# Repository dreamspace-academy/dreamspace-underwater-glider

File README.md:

# Underwater Glider

## **Motivation**

### Blue Econemy
Sri Lanka is an island country, located in the Indian Ocean, with a coastline of 1,585 km long, and the country claims an Exclusive Economic Zone (EEZ) extending 200 nautical miles, which is approximately 6.7 times Sri Lanka's land area. [1]

### Life Below Water
The world’s waters – their temperature, chemistry, currents and life – drive global systems that make the Earth habitable. How we manage this vital resource is essential for life on earth, and to counterbalance the effects of climate change. [2]

## **Problem**

### Real-time Monitoring
To keep our water ecosystem safe, secure, clean and sustainable, we need to measure various parameters in real-time. Sri Lanka, being a country that was devastated by 30 years of war, doesn’t even have the basic infrastructure, such as roads, in many parts of the country.

Therefore it is understandable that there is no modern infrastructure in Sri Lanka to measure and monitor the water ecosystems. Such equipment is very crucial for scientific research and assessment on an ecosystem, which is swiftly changing due to various weather conditions. [3]

### Affordability
The coastline and adjacent waters support highly productive marine ecosystems, and provide a massive economic value to this small nation, while this unique geographical position is highly contested by global powers.

## **Solution**

### Open-source Underwater Glider (OSUG)
There has been a breakthrough with low cost autonomous underwater vehicles, and as this capability has matured a wide range of hobby and commercial applications have been developed. However, there are no affordable extended duration underwater exploration platforms and this project aims to address this need.

Alex Williams, a young innovator from the USA, has developed a low cost and versatile underwater glider capable of extended missions of up to weeks at a time; using commodity hardware, 3D printed parts and an open-source autopilot. Furthermore, he won the Grand Prize in the Hackaday Prize Challenge 2017. [4]

### Underwater Gliding
Underwater gliders use a buoyancy engine to change the mass of the glider, allowing them to ascend and descend through the water. With power only being used to power the engine intermittently, gliders can typically run for weeks or months without recharge, making them ideal for environmental monitoring. As underwater gliders travel slowly through the water, they disturb the surrounding water very little, allowing for accurate and reliable data recording. [5]

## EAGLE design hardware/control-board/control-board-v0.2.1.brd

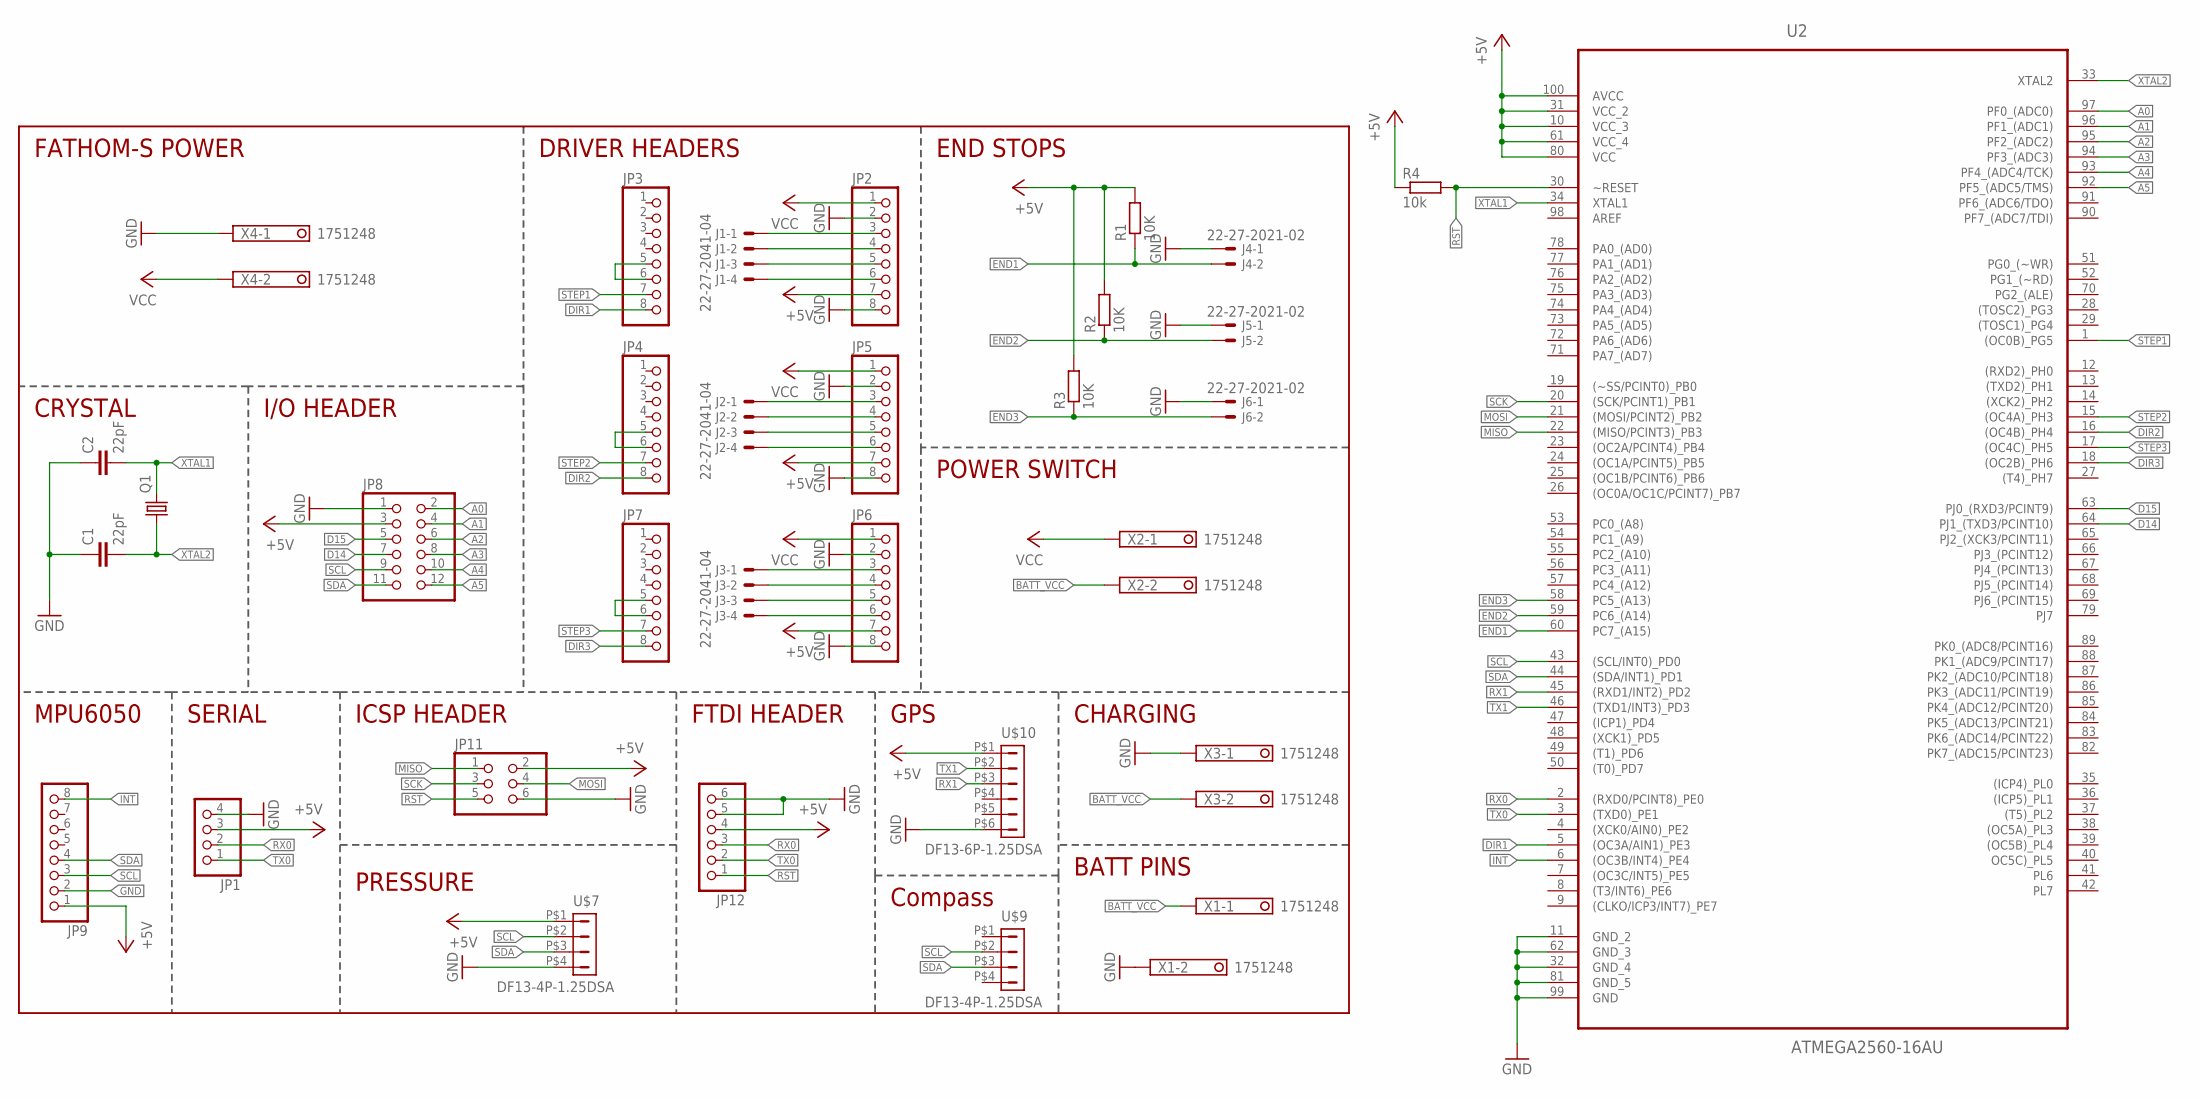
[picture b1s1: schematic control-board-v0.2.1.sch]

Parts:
C1, C2: 22pF; C0603
J1, J2, J3: 22-27-2041-04; 6410-04
J4, J5, J6: 22-27-2021-02; 6410-02
JP1: PINHD-1X4; 1X04
JP2, JP3, JP4, JP5, JP6, JP7, JP9: PINHD-1X8; 1X08
JP8: PINHD-2X6; 2X06
JP11: PINHD-2X3; 2X03
JP12: PINHD-1X6; 1X06
Q1: CRYSTALHC49U70; HC49U70
R1, R2, R3: 10K; R0603
R4: 10k; R0603
U2: ATMEGA2560-16AU; QFP50P1600X1600X120-100N
U$7, U$9: DF13-4P-1.25DSA
U$10: DF13-6P-1.25DSA
X1, X2, X3, X4: 1751248

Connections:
+5V: JP1.3, JP2.7, JP5.7, JP6.7, JP8.3, JP9.1, JP11.2, JP12.4, R1.2, R2.2, R3.2, R4.1, U2.10 (VCC_3), U2.31 (VCC_2), U2.61 (VCC_4), U2.80 (VCC), U2.100 (AVCC), U$7.P$1 (1), U$10.P$1 (1)
A0: JP8.2, U2.97 (PF0_(ADC0))
A1: JP8.4, U2.96 (PF1_(ADC1))
A2: JP8.6, U2.95 (PF2_(ADC2))
A3: JP8.8, U2.94 (PF3_(ADC3))
A4: JP8.10, U2.93 (PF4_(ADC4/TCK))
A5: JP8.12, U2.92 (PF5_(ADC5/TMS))
BATT_VCC: X1.1, X2.2, X3.2
D14: JP8.7, U2.64 (PJ1_(TXD3/PCINT10))
D15: JP8.5, U2.63 (PJ0_(RXD3/PCINT9))
DIR1: JP3.8, U2.5 ((OC3A/AIN1)_PE3)
DIR2: JP4.8, U2.16 ((OC4B)_PH4)
DIR3: JP7.8, U2.18 ((OC2B)_PH6)
END1: J4.2, R1.1, U2.60 (PC7_(A15))
END2: J5.2, R2.1, U2.59 (PC6_(A14))
END3: J6.2, R3.1, U2.58 (PC5_(A13))
GND: C1.1, C2.1, J4.1, J5.1, J6.1, JP1.4, JP2.2, JP2.8, JP5.2, JP5.8, JP6.2, JP6.8, JP8.1, JP9.2, JP11.6, JP12.5, JP12.6, U2.11 (GND_2), U2.32 (GND_4), U2.62 (GND_3), U2.81 (GND_5), U2.99 (GND), U$7.P$4 (4), U$10.P$6 (6), X1.2, X3.1, X4.1
INT: JP9.8, U2.6 ((OC3B/INT4)_PE4)
MISO: JP11.1, U2.22 ((MISO/PCINT3)_PB3)
MOSI: JP11.4, U2.21 ((MOSI/PCINT2)_PB2)
unnamed: JP3.5, JP3.6
unnamed: JP4.5, JP4.6
unnamed: J1.4, JP2.6
unnamed: JP7.5, JP7.6
unnamed: J1.3, JP2.5
unnamed: J1.2, JP2.4
unnamed: J1.1, JP2.3
unnamed: J2.4, JP5.6
unnamed: J2.3, JP5.5
unnamed: J2.2, JP5.4
unnamed: J2.1, JP5.3
unnamed: J3.4, JP6.6
unnamed: J3.3, JP6.5
unnamed: J3.2, JP6.4
unnamed: J3.1, JP6.3
RST: JP11.5, JP12.1, R4.2, U2.30 (~RESET)
RX0: JP1.2, JP12.3, U2.2 ((RXD0/PCINT8)_PE0)
RX1: U2.45 ((RXD1/INT2)_PD2), U$10.P$3 (3)
SCK: JP11.3, U2.20 ((SCK/PCINT1)_PB1)
SCL: JP8.9, JP9.3, U2.43 ((SCL/INT0)_PD0), U$7.P$2 (2), U$9.P$2 (2)
SDA: JP8.11, JP9.4, U2.44 ((SDA/INT1)_PD1), U$7.P$3 (3), U$9.P$3 (3)
STEP1: JP3.7, U2.1 ((OC0B)_PG5)
STEP2: JP4.7, U2.15 ((OC4A)_PH3)
STEP3: JP7.7, U2.17 ((OC4C)_PH5)
TX0: JP1.1, JP12.2, U2.3 ((TXD0)_PE1)
TX1: U2.46 ((TXD1/INT3)_PD3), U$10.P$2 (2)
VCC: JP2.1, JP5.1, JP6.1, X2.1, X4.2
XTAL1: C2.2, Q1.2, U2.34 (XTAL1)
XTAL2: C1.2, Q1.1, U2.33 (XTAL2)

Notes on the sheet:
MPU6050
DRIVER HEADERS
BATT PINS
END STOPS
SERIAL
ICSP HEADER
FTDI HEADER
GPS
Compass
CHARGING
PRESSURE
POWER SWITCH
FATHOM-S POWER
CRYSTAL
I/O HEADER

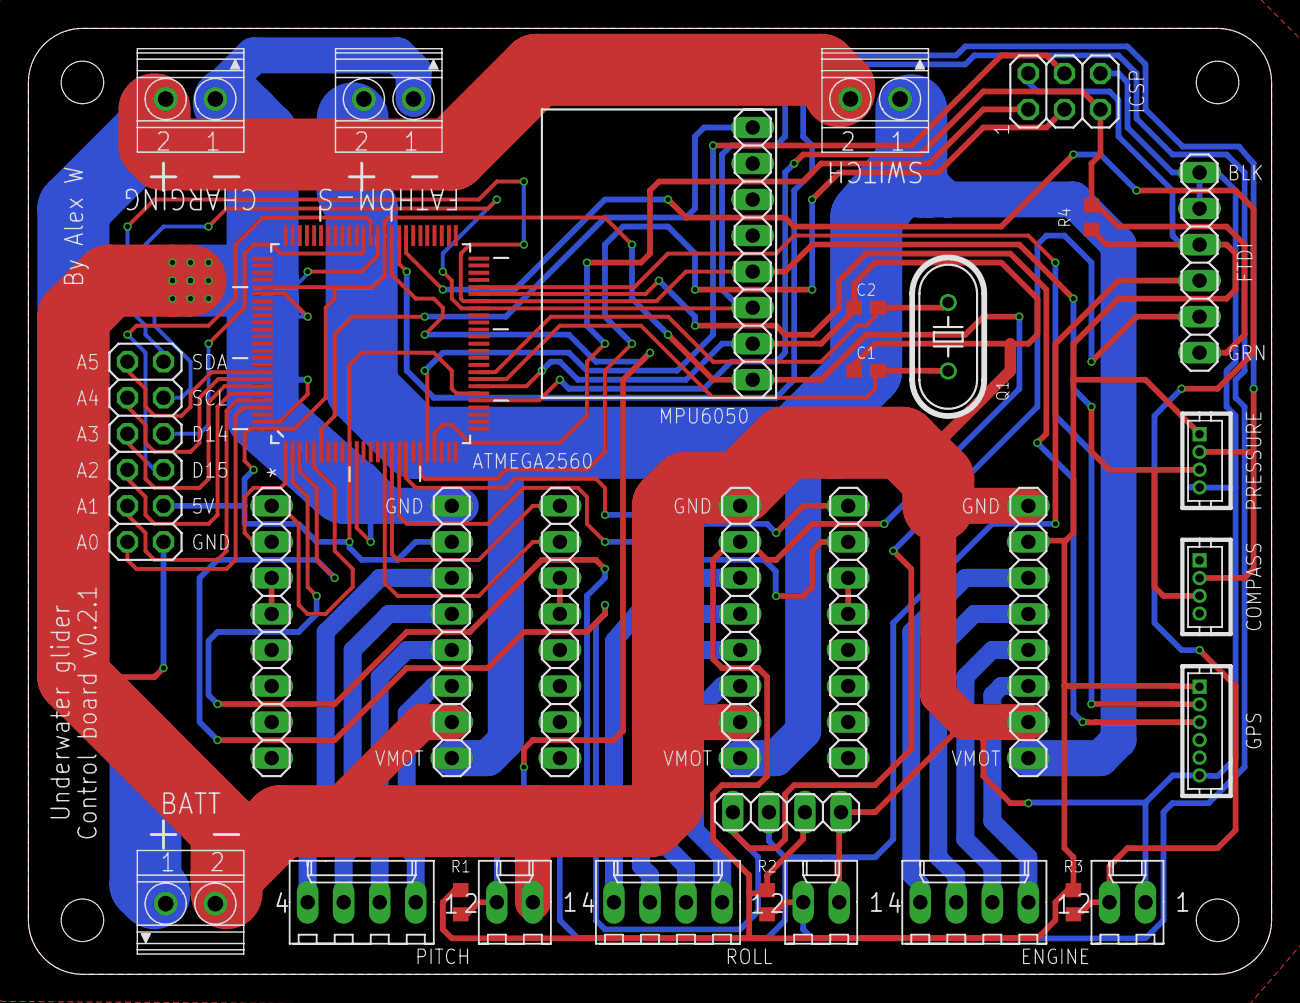
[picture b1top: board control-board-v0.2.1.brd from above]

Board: 2 copper layers, 87.6 x 66.7 mm, 32 parts (0 on the bottom side), 49 nets.

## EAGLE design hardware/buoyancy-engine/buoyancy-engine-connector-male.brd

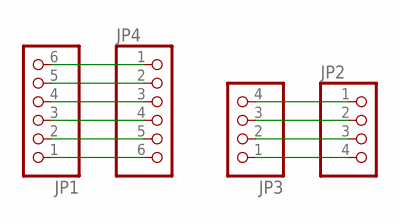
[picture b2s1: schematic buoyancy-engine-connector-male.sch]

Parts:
JP1, JP4: PINHD-1X6; 1X06
JP2, JP3: PINHD-1X4; 1X04

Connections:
unnamed: JP2.1, JP3.4
unnamed: JP2.2, JP3.3
unnamed: JP2.3, JP3.2
unnamed: JP2.4, JP3.1
unnamed: JP1.6, JP4.1
unnamed: JP1.5, JP4.2
unnamed: JP1.4, JP4.3
unnamed: JP1.3, JP4.4
unnamed: JP1.2, JP4.5
unnamed: JP1.1, JP4.6

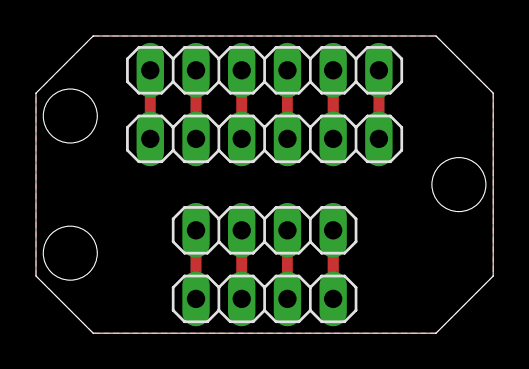
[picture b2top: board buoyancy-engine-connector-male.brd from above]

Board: 2 copper layers, 25.4 x 16.5 mm, 4 parts (0 on the bottom side), 10 nets.

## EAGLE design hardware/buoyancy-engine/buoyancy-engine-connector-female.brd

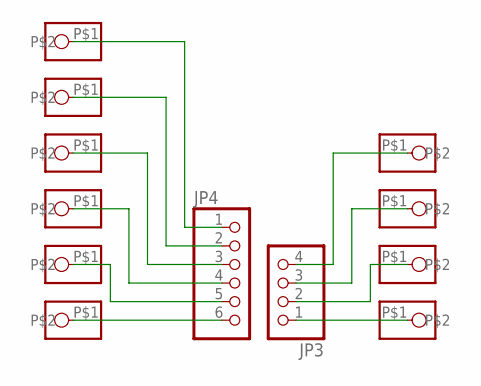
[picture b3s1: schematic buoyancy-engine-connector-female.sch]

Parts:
JP3: PINHD-1X4; 1X04
JP4: PINHD-1X6; 1X06
U$1, U$2, U$3, U$4, U$5, U$6, U$7, U$8, U$9, U$10: POGO-PIN-PAD

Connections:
unnamed: JP3.4, U$10.P$1
unnamed: JP3.3, U$7.P$1
unnamed: JP3.2, U$8.P$1
unnamed: JP3.1, U$9.P$1
unnamed: JP4.1, U$6.P$1
unnamed: JP4.2, U$5.P$1
unnamed: JP4.3, U$4.P$1
unnamed: JP4.4, U$3.P$1
unnamed: JP4.5, U$2.P$1
unnamed: JP4.6, U$1.P$1

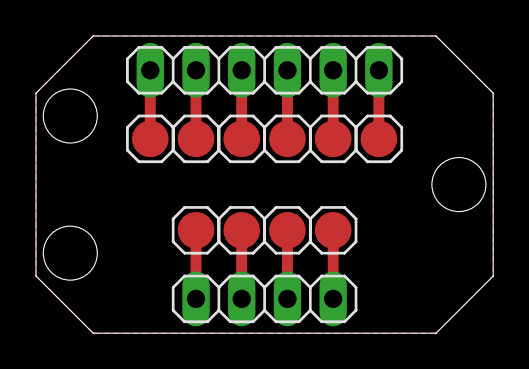
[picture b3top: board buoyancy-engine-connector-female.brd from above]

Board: 2 copper layers, 25.4 x 16.5 mm, 12 parts (0 on the bottom side), 10 nets.

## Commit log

2020-07-06 Add 3d printing manufacturing files
2020-07-06 Add laser cutting parts
2020-07-06 Add gearbox design files
2020-07-06 Add buoyancy engine eagle pcb design files
2020-07-06 Add control board eagle pcb design files
2020-07-06 Add pcb manufacturing files
2020-07-06 Clean files
2020-07-06 Add test 3d print files
2020-07-06 Add control firmware
2020-07-06 Add image files
2020-07-06 Add docs files
2020-07-06 Move gdocs to the drive
